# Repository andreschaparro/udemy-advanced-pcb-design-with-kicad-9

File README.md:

# udemy | Advanced PCB Design with KiCad 9

Dr. Peter Dalmaris

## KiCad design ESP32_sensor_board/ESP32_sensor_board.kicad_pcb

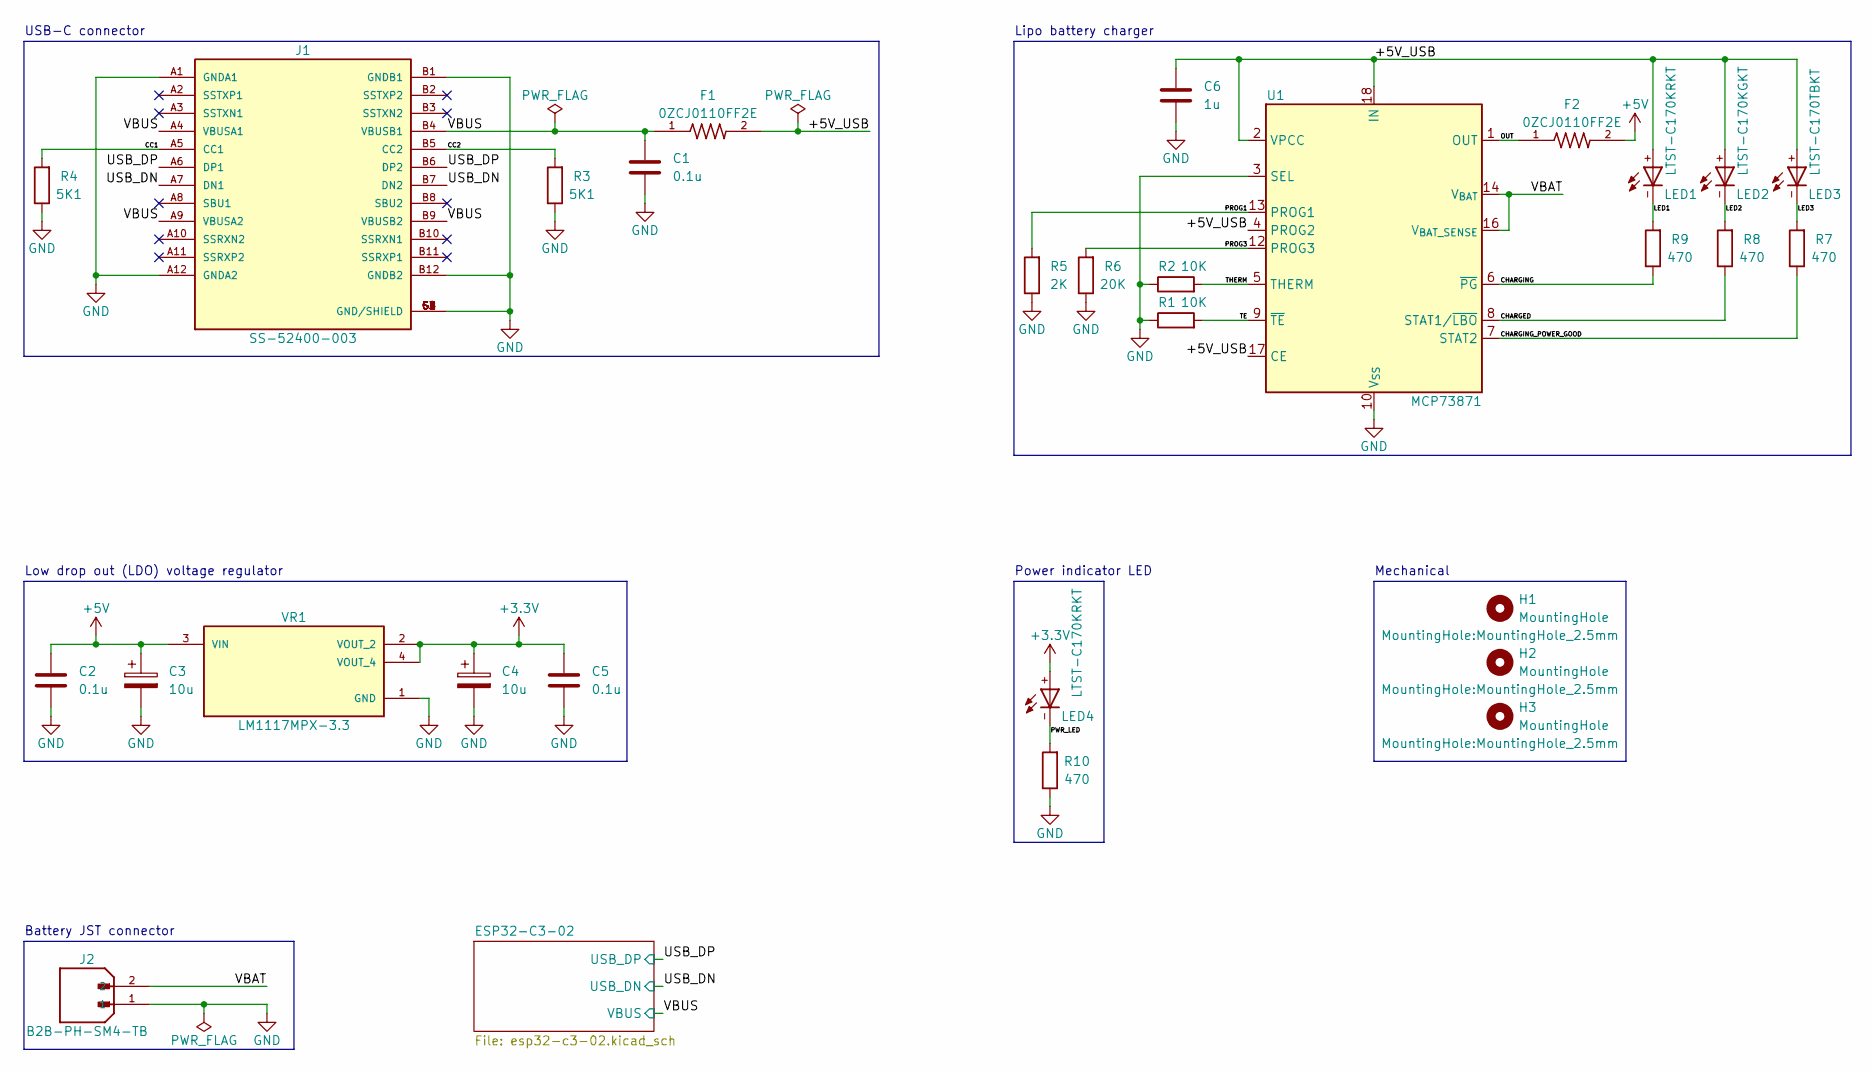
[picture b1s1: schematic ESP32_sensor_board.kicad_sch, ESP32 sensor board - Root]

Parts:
C1, C2, C5: 0.1u; C_0805_2012Metric
C3, C4: 10u; T491A106K010AT
C6: 1u; C_0805_2012Metric
F1, F2: 0ZCJ0110FF2E; RESC3216X125N
H1, H2, H3: MountingHole; MountingHole_2.5mm
J1: SS-52400-003; BELFUSE_SS-52400-003; PARTREV A0
J2: B2B-PH-SM4-TB; JST_B2B-PH-SM4-TB; PARTREV N/A
LED1, LED4: LTST-C170KRKT; DIOC200X125X110
LED2: LTST-C170KGKT; DIOC200X125X110
LED3: LTST-C170TBKT; DIOC200X125X110
R1, R2: 10K; R_0805_2012Metric
R3, R4: 5K1; R_0805_2012Metric
R5: 2K; R_0805_2012Metric
R6: 20K; R_0805_2012Metric
R7, R8, R9, R10: 470; R_0805_2012Metric
U1: MCP73871; QFN-20-1EP_4x4mm_P0.5mm_EP2.5x2.5mm
VR1: LM1117MPX-3.3; VREG_LM1117MPX-3.3; PARTREV O

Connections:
+3.3V: C4.1, C5.1, LED4.+, VR1.2 (VOUT_2), VR1.4 (VOUT_4); also elsewhere on the board
+5V: C2.1, C3.1, F2.2, VR1.3 (VIN)
/+5V_USB: C6.1, F1.2, LED1.+, LED2.+, LED3.+, U1.2 (VPCC), U1.4 (PROG2), U1.17 (CE), U1.18 (IN), U1.19 (IN)
/CC1: J1.A5 (CC1), R4.2
/CC2: J1.B5 (CC2), R3.2
/CHARGED: R8.1, U1.8 (STAT1/~LBO)
/CHARGING: R9.1, U1.6 (~PG)
/CHARGING_POWER_GOOD: R7.1, U1.7 (STAT2)
/LED1: LED1.-, R9.2
/LED2: LED2.-, R8.2
/LED3: LED3.-, R7.2
/OUT: F2.1, U1.1 (OUT), U1.20 (OUT)
/PROG1: R5.2, U1.13 (PROG1)
/PROG3: R6.2, U1.12 (PROG3)
/PWR_LED: LED4.-, R10.2
/TE: R1.2, U1.9 (~TE)
/THERM: R2.2, U1.5 (THERM)
/USB_DN: J1.A7 (DN1), J1.B7 (DN2); also elsewhere on the board
/USB_DP: J1.A6 (DP1), J1.B6 (DP2); also elsewhere on the board
/VBAT: J2.2, U1.14 (V_{BAT}), U1.15 (V_{BAT}), U1.16 (V_{BAT_SENSE})
/VBUS: C1.1, F1.1, J1.A4 (VBUSA1), J1.A9 (VBUSA2), J1.B4 (VBUSB1), J1.B9 (VBUSB2); also elsewhere on the board
GND: C1.2, C2.2, C3.2, C4.2, C5.2, C6.2, J1.A1 (GNDA1), J1.A12 (GNDA2), J1.B1 (GNDB1), J1.B12 (GNDB2), J1.G1 (GND/SHIELD), J1.G2 (GND/SHIELD), J1.G3 (GND/SHIELD), J1.G4 (GND/SHIELD), J1.S1 (GND/SHIELD), J1.S2 (GND/SHIELD), J1.S3 (GND/SHIELD), J1.S4 (GND/SHIELD), J2.1, R1.1, R2.1, R3.1, R4.1, R5.1, R6.1, R10.1, U1.3 (SEL), U1.10 (V_{SS}), U1.11 (V_{SS}), U1.21 (V_{SS}), VR1.1 (GND); also elsewhere on the board

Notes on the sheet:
Mechanical
Low drop out (LDO) voltage regulator
Power indicator LED
Battery JST connector
Lipo battery charger
USB-C connector

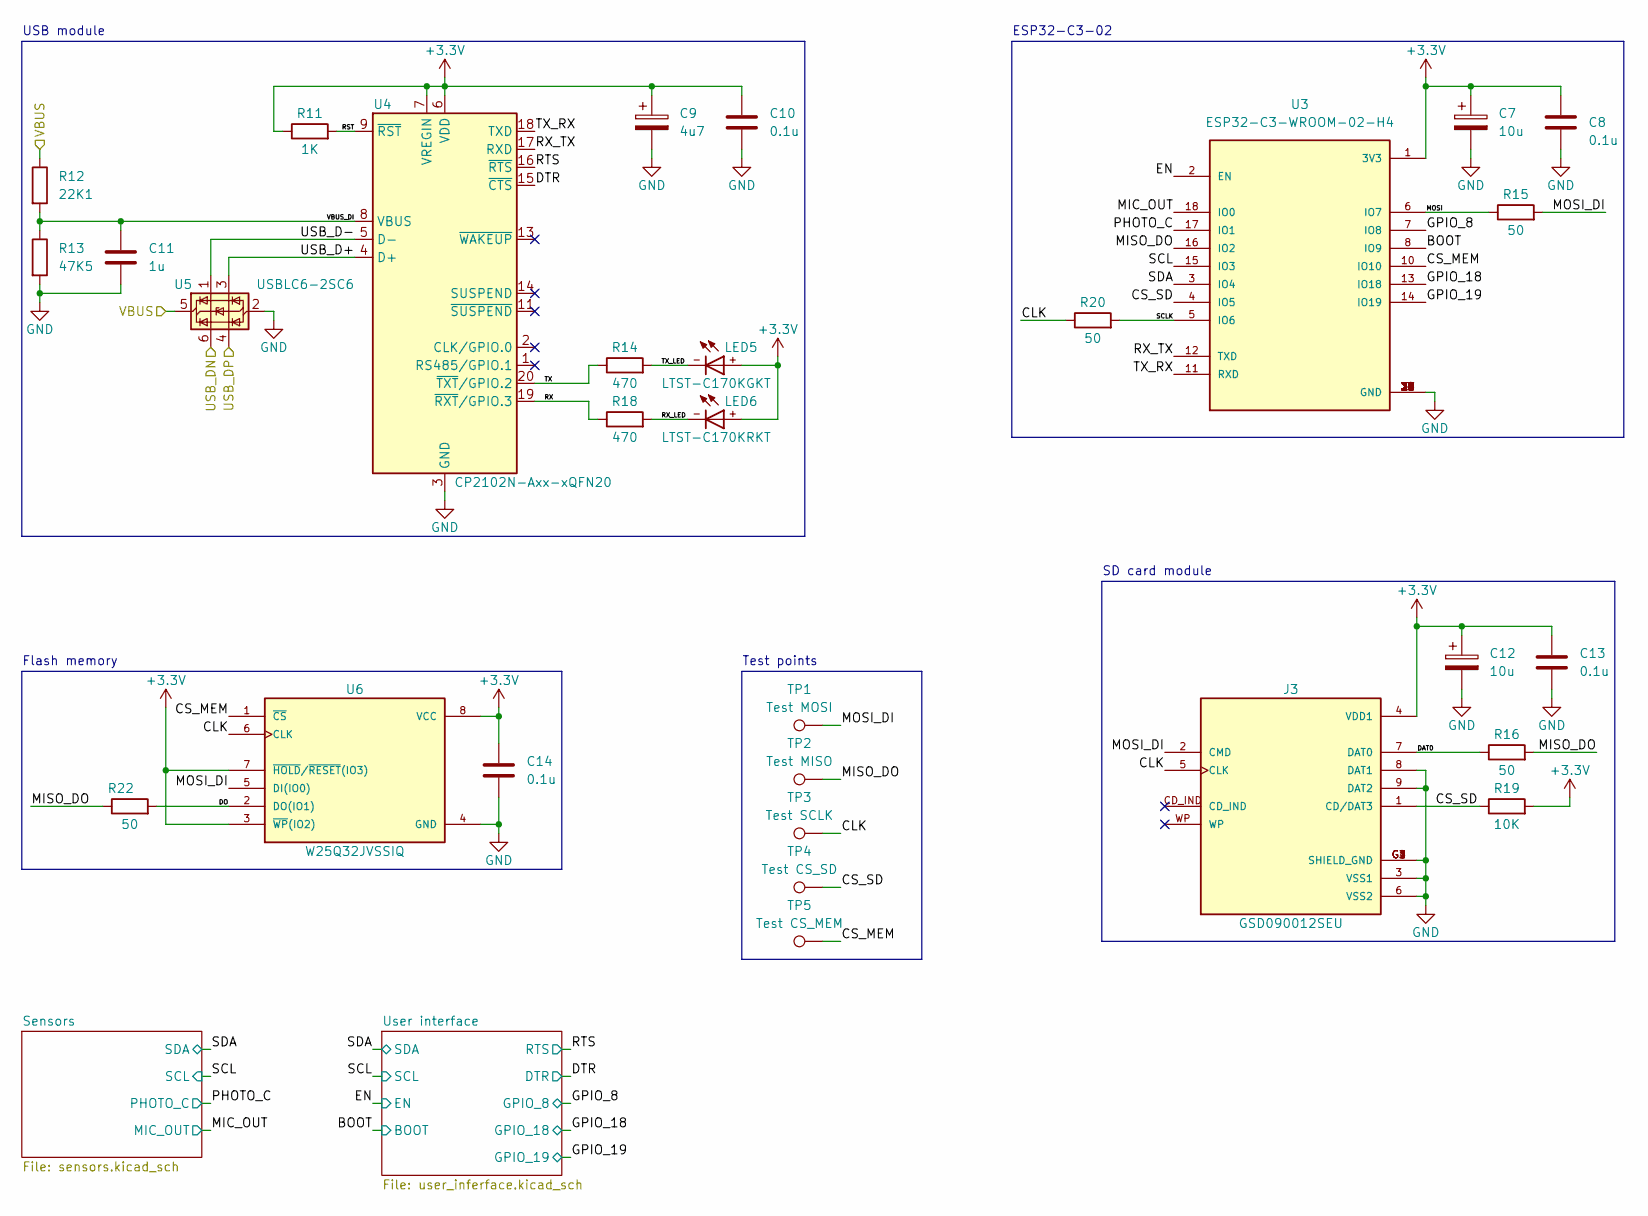
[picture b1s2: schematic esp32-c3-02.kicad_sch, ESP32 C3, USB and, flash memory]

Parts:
C7, C12: 10u; T491A106K010AT
C8, C10, C13, C14: 0.1u; C_0805_2012Metric
C9: 4u7; T491A106K010AT
C11: 1u; C_0805_2012Metric
J3: GSD090012SEU; AMPHENOL_GSD090012SEU; PARTREV E
LED5: LTST-C170KGKT; DIOC200X125X110
LED6: LTST-C170KRKT; DIOC200X125X110
R11: 1K; R_0805_2012Metric
R12: 22K1; R_0805_2012Metric
R13: 47K5; R_0805_2012Metric
R14, R18: 470; R_0805_2012Metric
R15, R16, R20, R22: 50; R_0805_2012Metric
R19: 10K; R_0805_2012Metric
TP1: Test MOSI; TestPoint_Pad_D1.0mm
TP2: Test MISO; TestPoint_Pad_D1.0mm
TP3: Test SCLK; TestPoint_Pad_D1.0mm
TP4: Test CS_SD; TestPoint_Pad_D1.0mm
TP5: Test CS_MEM; TestPoint_Pad_D1.0mm
U3: ESP32-C3-WROOM-02-H4; MODULE_ESP32-C3-WROOM-02-H4
U4: CP2102N-Axx-xQFN20; WFQFN-20
U5: USBLC6-2SC6; SOT-23-6
U6: W25Q32JVSSIQ; SOIC127P790X216-8N; M_PART_NUMBER W25QXX

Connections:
+3.3V: C7.1, C8.1, C9.1, C10.1, C12.1, C13.1, C14.1, J3.4 (VDD1), LED5.+, LED6.+, R11.1, R19.2, U3.1 (3V3), U4.6 (VDD), U4.7 (VREGIN), U6.3 (~WP(IO2)), U6.7 (~HOLD/~RESET(IO3)), U6.8 (VCC); also elsewhere on the board
/ESP32-C3-02/BOOT: U3.8 (IO9); also elsewhere on the board
/ESP32-C3-02/CLK: J3.5 (CLK), R20.1, TP3.1, U6.6 (CLK)
/ESP32-C3-02/CS_MEM: TP5.1, U3.10 (IO10), U6.1 (~CS)
/ESP32-C3-02/CS_SD: J3.1 (CD/DAT3), R19.1, TP4.1, U3.4 (IO5)
/ESP32-C3-02/DAT0: J3.7 (DAT0), R16.1
/ESP32-C3-02/DO: R22.2, U6.2 (DO(IO1))
/ESP32-C3-02/DTR: U4.15 (~CTS); also elsewhere on the board
/ESP32-C3-02/EN: U3.2 (EN); also elsewhere on the board
/ESP32-C3-02/GPIO_8: U3.7 (IO8); also elsewhere on the board
/ESP32-C3-02/GPIO_18: U3.13 (IO18); also elsewhere on the board
/ESP32-C3-02/GPIO_19: U3.14 (IO19); also elsewhere on the board
/ESP32-C3-02/MIC_OUT: U3.18 (IO0); also elsewhere on the board
/ESP32-C3-02/MISO_DO: R16.2, R22.1, TP2.1, U3.16 (IO2)
/ESP32-C3-02/MOSI: R15.1, U3.6 (IO7)
/ESP32-C3-02/MOSI_DI: J3.2 (CMD), R15.2, TP1.1, U6.5 (DI(IO0))
/ESP32-C3-02/PHOTO_C: U3.17 (IO1); also elsewhere on the board
/ESP32-C3-02/RST: R11.2, U4.9 (~RST)
/ESP32-C3-02/RTS: U4.16 (~RTS); also elsewhere on the board
/ESP32-C3-02/RX: R18.1, U4.19 (~RXT/GPIO.3)
/ESP32-C3-02/RX_LED: LED6.-, R18.2
/ESP32-C3-02/RX_TX: U3.12 (TXD), U4.17 (RXD)
/ESP32-C3-02/SCL: U3.15 (IO3); also elsewhere on the board
/ESP32-C3-02/SCLK: R20.2, U3.5 (IO6)
/ESP32-C3-02/SDA: U3.3 (IO4); also elsewhere on the board
/ESP32-C3-02/TX: R14.1, U4.20 (~TXT/GPIO.2)
/ESP32-C3-02/TX_LED: LED5.-, R14.2
/ESP32-C3-02/TX_RX: U3.11 (RXD), U4.18 (TXD)
/ESP32-C3-02/USB_D+: U4.4 (D+), U5.3 (I/O2)
/ESP32-C3-02/USB_D-: U4.5 (D-), U5.1 (I/O1)
/ESP32-C3-02/VBUS_DI: C11.1, R12.2, R13.1, U4.8 (VBUS)
/USB_DN: U5.6 (I/O1); also elsewhere on the board
/USB_DP: U5.4 (I/O2); also elsewhere on the board
/VBUS: R12.1, U5.5 (VBUS); also elsewhere on the board
GND: C7.2, C8.2, C9.2, C10.2, C11.2, C12.2, C13.2, C14.2, J3.3 (VSS1), J3.6 (VSS2), J3.8 (DAT1), J3.9 (DAT2), J3.G1 (SHIELD_GND), J3.G2 (SHIELD_GND), J3.G3 (SHIELD_GND), J3.G4 (SHIELD_GND), R13.2, U3.9 (GND), U3.19 (GND), U3.20 (GND), U3.21 (GND), U3.22 (GND), U3.23 (GND), U3.24 (GND), U3.25 (GND), U3.26 (GND), U3.27 (GND), U3.28 (GND), U3.29 (GND), U3.30 (GND), U3.31 (GND), U3.32 (GND), U3.33 (GND), U3.34 (GND), U3.35 (GND), U3.36 (GND), U3.37 (GND), U3.38 (GND), U3.39 (GND), U4.3 (GND), U4.12 (GND), U4.21 (GND), U5.2 (GND), U6.4 (GND); also elsewhere on the board

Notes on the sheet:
USB module
ESP32-C3-02
SD card module
Test points
Flash memory

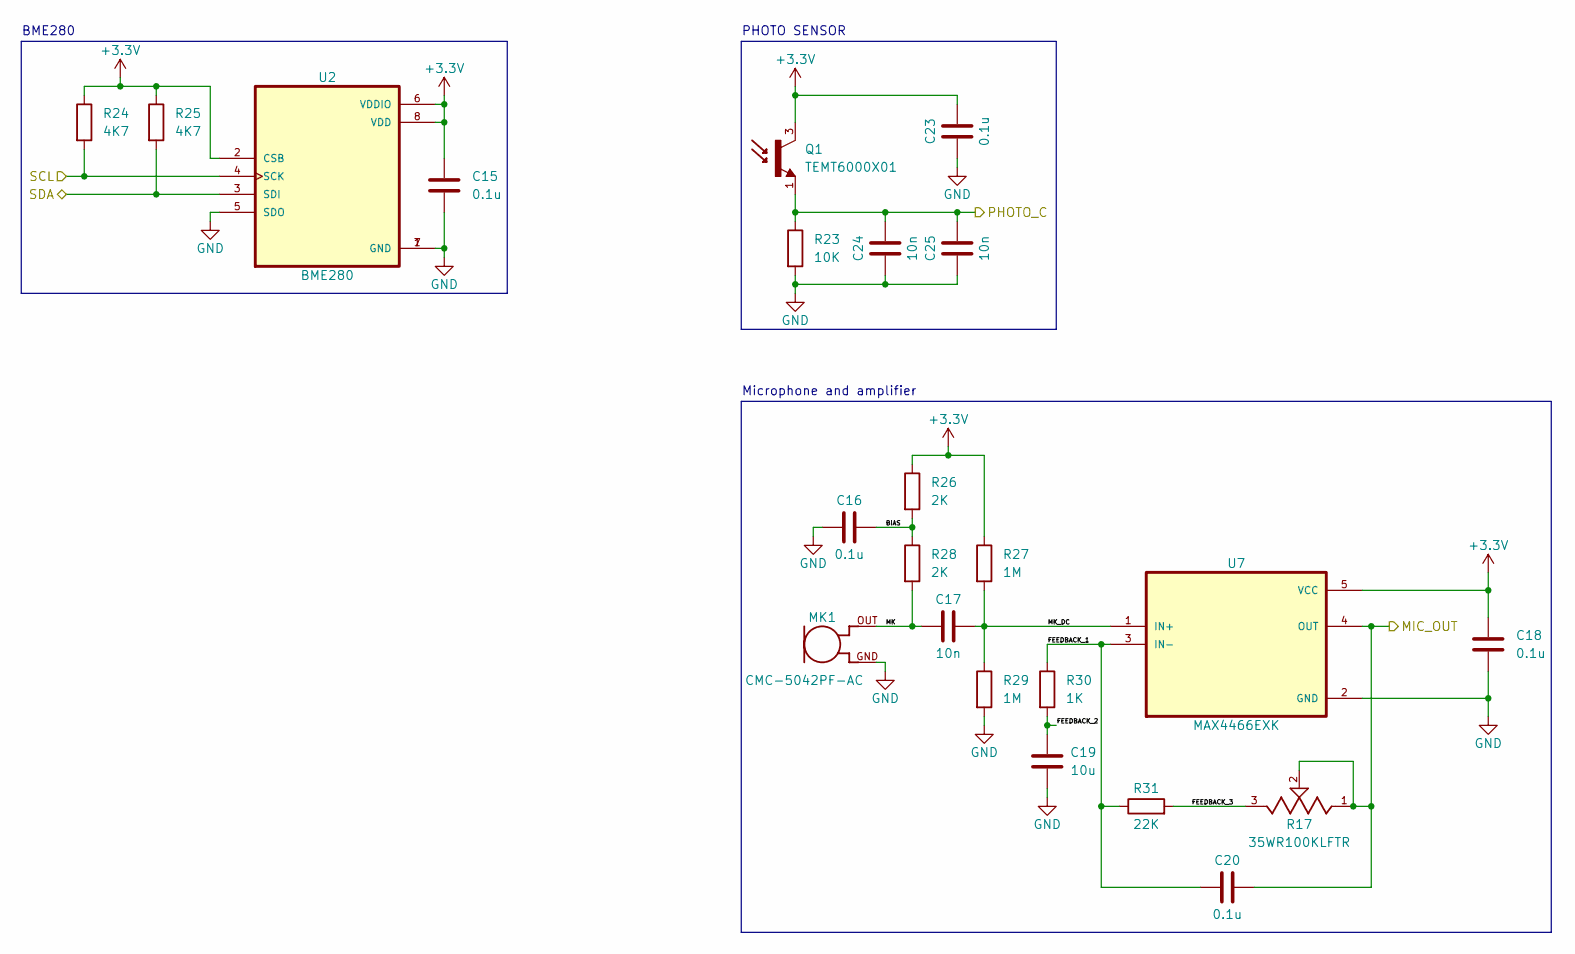
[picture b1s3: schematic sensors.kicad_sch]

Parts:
C15, C16, C18, C20, C23: 0.1u; C_0805_2012Metric
C17, C24, C25: 10n; C_0805_2012Metric
C19: 10u; C_0805_2012Metric
MK1: CMC-5042PF-AC; CUI_CMC-5042PF-AC
Q1: TEMT6000X01; TRANS_TEMT6000X01; PARTREV 1.9
R17: 35WR100KLFTR; TRIM_35WR100KLFTR; PARTREV D
R23: 10K; R_0805_2012Metric
R24, R25: 4K7; R_0805_2012Metric
R26, R28: 2K; R_0805_2012Metric
R27, R29: 1M; R_0805_2012Metric
R30: 1K; R_0805_2012Metric
R31: 22K; R_0805_2012Metric
U2: BME280; PSON65P250X250X100-8N
U7: MAX4466EXK; SOT65P210X110-5N

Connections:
+3.3V: C15.1, C18.1, C23.2, Q1.3, R24.1, R25.1, R26.1, R27.1, U2.2 (CSB), U2.6 (VDDIO), U2.8 (VDD), U7.5 (VCC); also elsewhere on the board
/ESP32-C3-02/MIC_OUT: C20.2, R17.1, R17.2, U7.4 (OUT); also elsewhere on the board
/ESP32-C3-02/PHOTO_C: C24.2, C25.2, Q1.1, R23.1; also elsewhere on the board
/ESP32-C3-02/SCL: R24.2, U2.4 (SCK); also elsewhere on the board
/ESP32-C3-02/SDA: R25.2, U2.3 (SDI); also elsewhere on the board
/ESP32-C3-02/Sensors/BIAS: C16.2, R26.2, R28.1
/ESP32-C3-02/Sensors/FEEDBACK_1: C20.1, R30.1, R31.1, U7.3 (IN-)
/ESP32-C3-02/Sensors/FEEDBACK_2: C19.1, R30.2
/ESP32-C3-02/Sensors/FEEDBACK_3: R17.3, R31.2
/ESP32-C3-02/Sensors/MK: C17.1, MK1.OUT, R28.2
/ESP32-C3-02/Sensors/MK_DC: C17.2, R27.2, R29.1, U7.1 (IN+)
GND: C15.2, C16.1, C18.2, C19.2, C23.1, C24.1, C25.1, MK1.GND, R23.2, R29.2, U2.1 (GND), U2.5 (SDO), U2.7 (GND), U7.2 (GND); also elsewhere on the board

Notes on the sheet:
Microphone and amplifier
PHOTO SENSOR
BME280

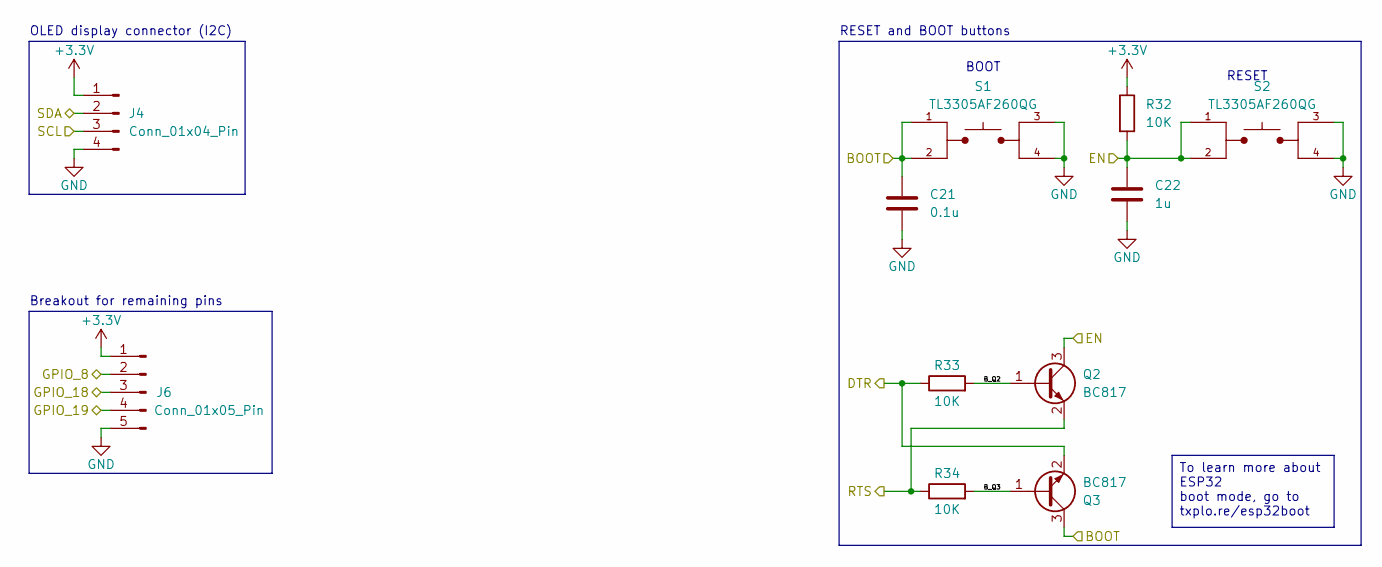
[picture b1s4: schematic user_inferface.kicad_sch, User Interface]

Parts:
C21: 0.1u; C_0805_2012Metric
C22: 1u; C_0805_2012Metric
J4: Conn_01x04_Pin; PinHeader_1x04_P2.54mm_Vertical
J6: Conn_01x05_Pin; PinHeader_1x05_P2.54mm_Vertical
Q2, Q3: BC817; SOT-23
R32, R33, R34: 10K; R_0805_2012Metric
S1, S2: TL3305AF260QG; SW_TL3305AF260QG; PARTREV C

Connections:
+3.3V: J4.1, J6.1, R32.1; also elsewhere on the board
/ESP32-C3-02/BOOT: C21.1, Q3.3 (C), S1.1, S1.2; also elsewhere on the board
/ESP32-C3-02/DTR: Q3.2 (E), R33.1; also elsewhere on the board
/ESP32-C3-02/EN: C22.1, Q2.3 (C), R32.2, S2.1, S2.2; also elsewhere on the board
/ESP32-C3-02/GPIO_8: J6.2; also elsewhere on the board
/ESP32-C3-02/GPIO_18: J6.3; also elsewhere on the board
/ESP32-C3-02/GPIO_19: J6.4; also elsewhere on the board
/ESP32-C3-02/RTS: Q2.2 (E), R34.1; also elsewhere on the board
/ESP32-C3-02/SCL: J4.3; also elsewhere on the board
/ESP32-C3-02/SDA: J4.2; also elsewhere on the board
/ESP32-C3-02/User interface/B_Q2: Q2.1 (B), R33.2
/ESP32-C3-02/User interface/B_Q3: Q3.1 (B), R34.2
GND: C21.2, C22.2, J4.4, J6.5, S1.3, S1.4, S2.3, S2.4; also elsewhere on the board

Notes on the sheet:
RESET
BOOT
RESET and BOOT buttons
OLED display connector (I2C)
Breakout for remaining pins
To learn more about ESP32 boot mode, go to txplo.re/esp32boot

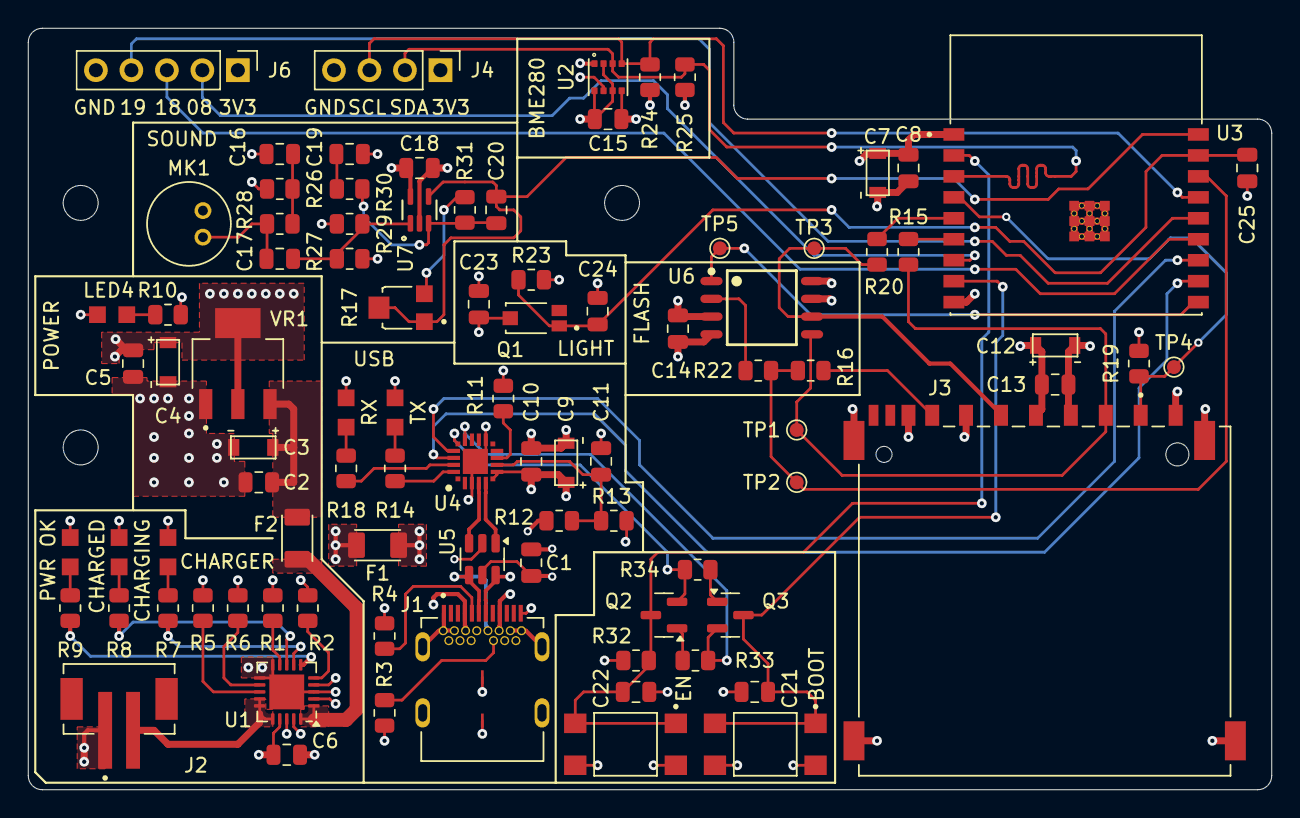
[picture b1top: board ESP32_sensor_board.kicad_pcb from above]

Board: 4 copper layers, 89.0 x 54.5 mm, 93 parts (0 on the bottom side), 60 nets.

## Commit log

2025-06-02 Schematic design section 1 completed
2025-06-03 Schematic design section 2 completed
2025-06-03 Schematic design section 3 completed
2025-06-04 Layout design section 1 completed
2025-06-04 Schematic design C19 added
2025-06-04 Layout design section 2 completed
2025-06-05 Layout design section 3 in progress
2025-06-05 Layout design section 3 completed
2025-06-09 Layout design section 4 completed
2025-06-09 Production section completed
2025-06-10 Prototype 2 completed
2025-06-10 Completed
